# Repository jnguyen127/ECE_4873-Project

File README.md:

# ECE4873 - Power Generation and Consumption Tracking
Repository revolved around using a clamp ammeter and microcontroller in order to monitor and track power consumption, and the data it recieves can be viewed on a web application. The folders included are as follow: "PowerTap" (Microcontroller program) and "Web_Application" (web application). The "MainPCB" (PCB cad) and "Lambda_Function" (automatically delete expired new accounts) are optional features of this device.

More information can be found on "Guide.html" by opening the file using any web browser.

* If you use this repo as a reference, make sure to give credit please.
* If there are any issues or concerns, please email John Nguyen: jhnguyen127@gmail.com!

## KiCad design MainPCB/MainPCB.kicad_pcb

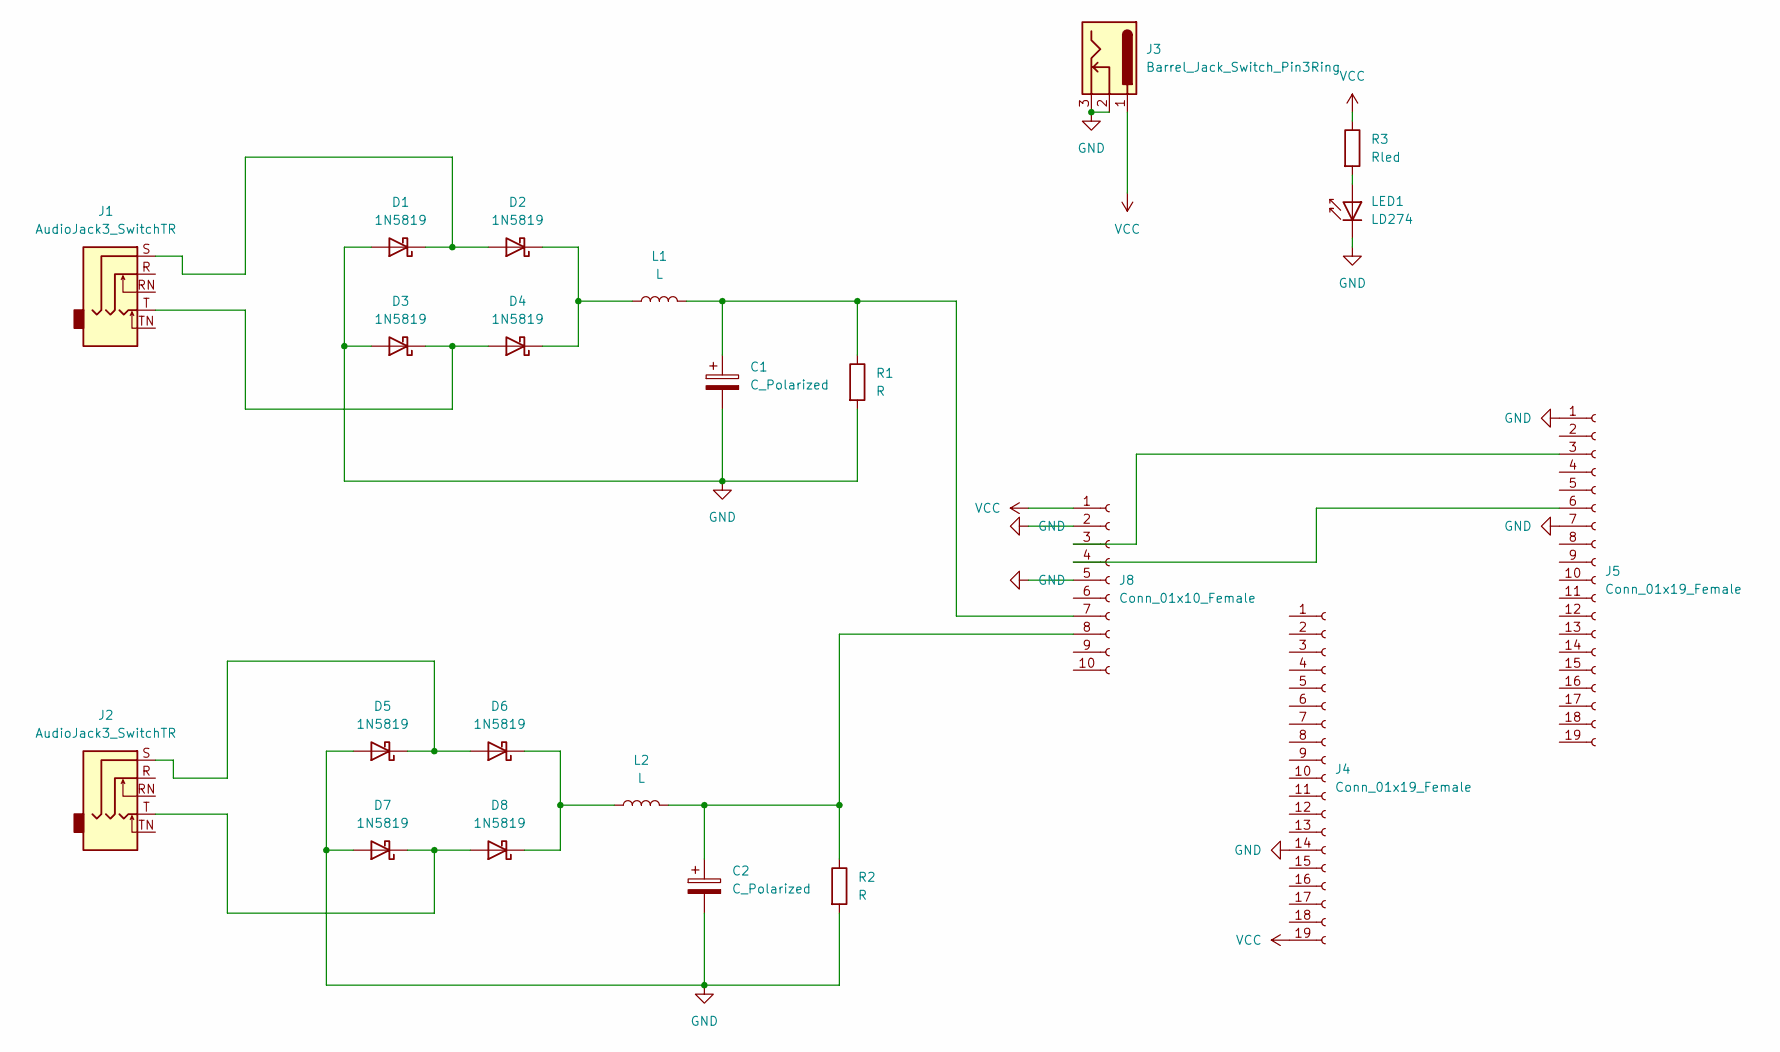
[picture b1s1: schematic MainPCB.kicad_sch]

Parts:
C1, C2: C_Polarized; C_Radial_D10.0mm_H20.0mm_P5.00mm
D1, D2, D3, D4, D5, D6, D7, D8: 1N5819; D_DO-41_SOD81_P10.16mm_Horizontal
J1, J2: AudioJack3_SwitchTR; Jack_3.5mm_Ledino_KB3SPRS_Horizontal
J3: Barrel_Jack_Switch_Pin3Ring; BarrelJack_Wuerth_6941xx301002
J4, J5: Conn_01x19_Female; PinHeader_1x19_P2.54mm_Vertical
J8: Conn_01x10_Female; PinHeader_1x10_P2.54mm_Vertical
L1, L2: L; L_Radial_D12.0mm_P5.00mm_Neosid_SD12k_style2
LED1: LD274; LED_D5.0mm_IRGrey
R1, R2: R; R_Axial_DIN0207_L6.3mm_D2.5mm_P10.16mm_Horizontal
R3: Rled; R_Axial_DIN0207_L6.3mm_D2.5mm_P10.16mm_Horizontal

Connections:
GND: C1.2, C2.2, D1.2 (A), D3.2 (A), D5.2 (A), D7.2 (A), J3.2, J3.3, J4.14, J5.1, J5.7, J8.2, J8.5, LED1.1 (K), R1.2, R2.2
unnamed: C1.1, J8.7, L1.2, R1.1
unnamed: C2.1, J8.8, L2.2, R2.1
unnamed: D1.1 (K), D2.2 (A), J1.S
unnamed: D2.1 (K), D4.1 (K), L1.1
unnamed: D3.1 (K), D4.2 (A), J1.T
unnamed: D5.1 (K), D6.2 (A), J2.S
unnamed: D6.1 (K), D8.1 (K), L2.1
unnamed: D7.1 (K), D8.2 (A), J2.T
unnamed: J5.3, J8.3
unnamed: J5.6, J8.4
unnamed: LED1.2 (A), R3.2
VCC: J3.1, J4.19, J8.1, R3.1

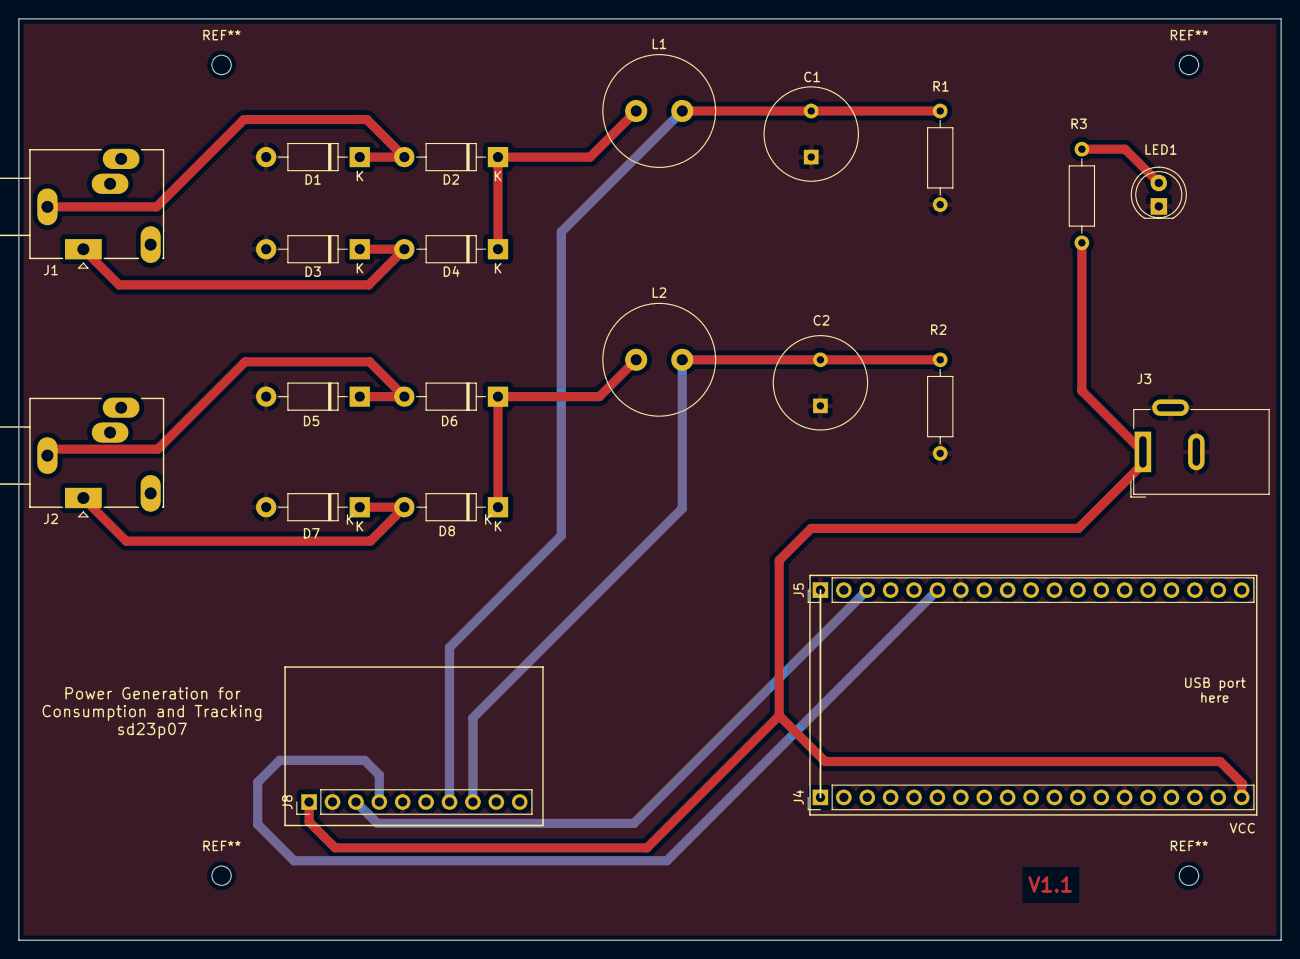
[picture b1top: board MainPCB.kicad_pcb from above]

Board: 2 copper layers, 137.0 x 100.0 mm, 22 parts (0 on the bottom side), 13 nets.
